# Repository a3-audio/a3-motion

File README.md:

# A³ Motion

The 4-channel motion sampler of [A³ Audio](https://github.com/a3-audio/a3-system).
It records movements on a touchscreen sphere and plays them back in time with
the beat, steering each channel's position on A³ Core over OSC.

This repository holds the panel firmware (`firmware/`, ESP32-S3) and the PCB and
housing designs (`hardware/`; the boards in `pcb/`, one folder per revision: `v1` the first boards (mainboard and button matrix), `v3_1` the current one). The touchscreen app is
[a3-motion-ui](https://github.com/a3-audio/a3-motion-ui), wired in here as the
submodule `a3-motion-ui` (named `ui` until 2026-10-31: every submodule path is
now its repository's name).

**Documentation: https://a3-audio.github.io/a3-doc/**

- [A³ Motion user guide](https://a3-audio.github.io/a3-doc/user/a3motion.html)
- [Configuration](https://a3-audio.github.io/a3-doc/configuration/moc.html),
  [Assembly](https://a3-audio.github.io/a3-doc/assembly/moc.html) and
  [Development](https://a3-audio.github.io/a3-doc/development/moc.html)

## Firmware

A PlatformIO project for the `esp32-s3-devkitc-1-n16r8`. Run from `firmware/`:

```bash
pio run                    # build
pio run -t upload          # flash
pio device monitor         # serial monitor, 115200 baud
pio test -e native         # host-side unit tests
python3 -m unittest test_host
```

Upload and monitor need no port. They find the panel by its USB ID, the CH343
bridge `1A86:55D3` (`build.hwids` in `boards/esp32-s3-devkitc-1-n16r8.json`).

`host.py` polls the firmware over serial and prints the decoded buttons,
encoders and pots (`python3 host.py`; needs `pyserial`). Its docstring lists
the options and describes the binary poll-frame protocol. Use it to tell a
firmware fault from a fault in the UI.

## The UI computer

Motion UI runs on any Linux machine with a touchscreen, and the panel connects
to it over USB. It is tested on a NUC (on the rig, the Core machine) and was
first planned for a Raspberry Pi 5; see
[Hardware](https://a3-audio.github.io/a3-doc/configuration/moc.html#moc-hardware)
in the docs. The i3 config, the X rules and the user service are in the UI
repository, under
[`platform_config/`](https://github.com/a3-audio/a3-motion-ui/tree/main/platform_config).

## License

REUSE-compliant: the licenses are in `LICENSES/`, which file has which is in
`.reuse/dep5`.

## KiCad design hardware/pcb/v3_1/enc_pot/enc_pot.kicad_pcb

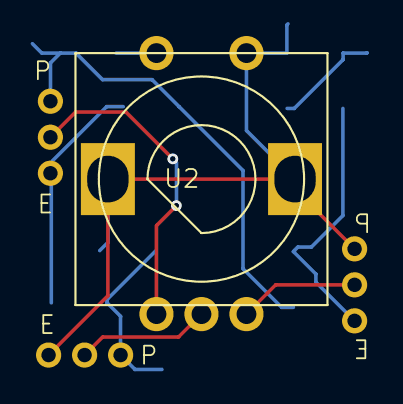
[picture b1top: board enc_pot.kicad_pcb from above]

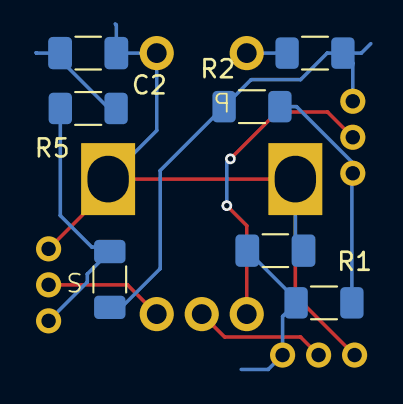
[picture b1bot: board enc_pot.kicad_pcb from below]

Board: 2 copper layers, 11 parts (10 on the bottom side), 10 nets.

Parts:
C1, C2: 100nF; C_1206_3216Metric_Pad1.33x1.80mm_HandSolder
R1, R5: 1k; R_1206_3216Metric_Pad1.30x1.75mm_HandSolder
R2, R4: 10K; R_1206_3216Metric_Pad1.30x1.75mm_HandSolder
R3: 10k; R_1206_3216Metric_Pad1.30x1.75mm_HandSolder
U1, U3, U4: a3_jumper_fix
U2: A3_ENC_POT_mix

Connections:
+3V3: R2.1, R3.2, R4.1, U1.S2
/EB/-: C2.1, R5.1
/ESW: R3.1, U2.S2
GND: C1.2, C2.2, U2.S1, U2.SH1 (shield), U2.SH2 (shield), U3.S2, U4.S1
unnamed: R1.2, R2.2, U1.S1
unnamed: R4.2, R5.2, U4.S2
unnamed: U1.S, U2.A (E1/PA)
unnamed: U2.B (E2/PB), U4.S
unnamed: U2.C (EGND/PW), U3.S
POT_H: C1.1, R1.1, U3.S1

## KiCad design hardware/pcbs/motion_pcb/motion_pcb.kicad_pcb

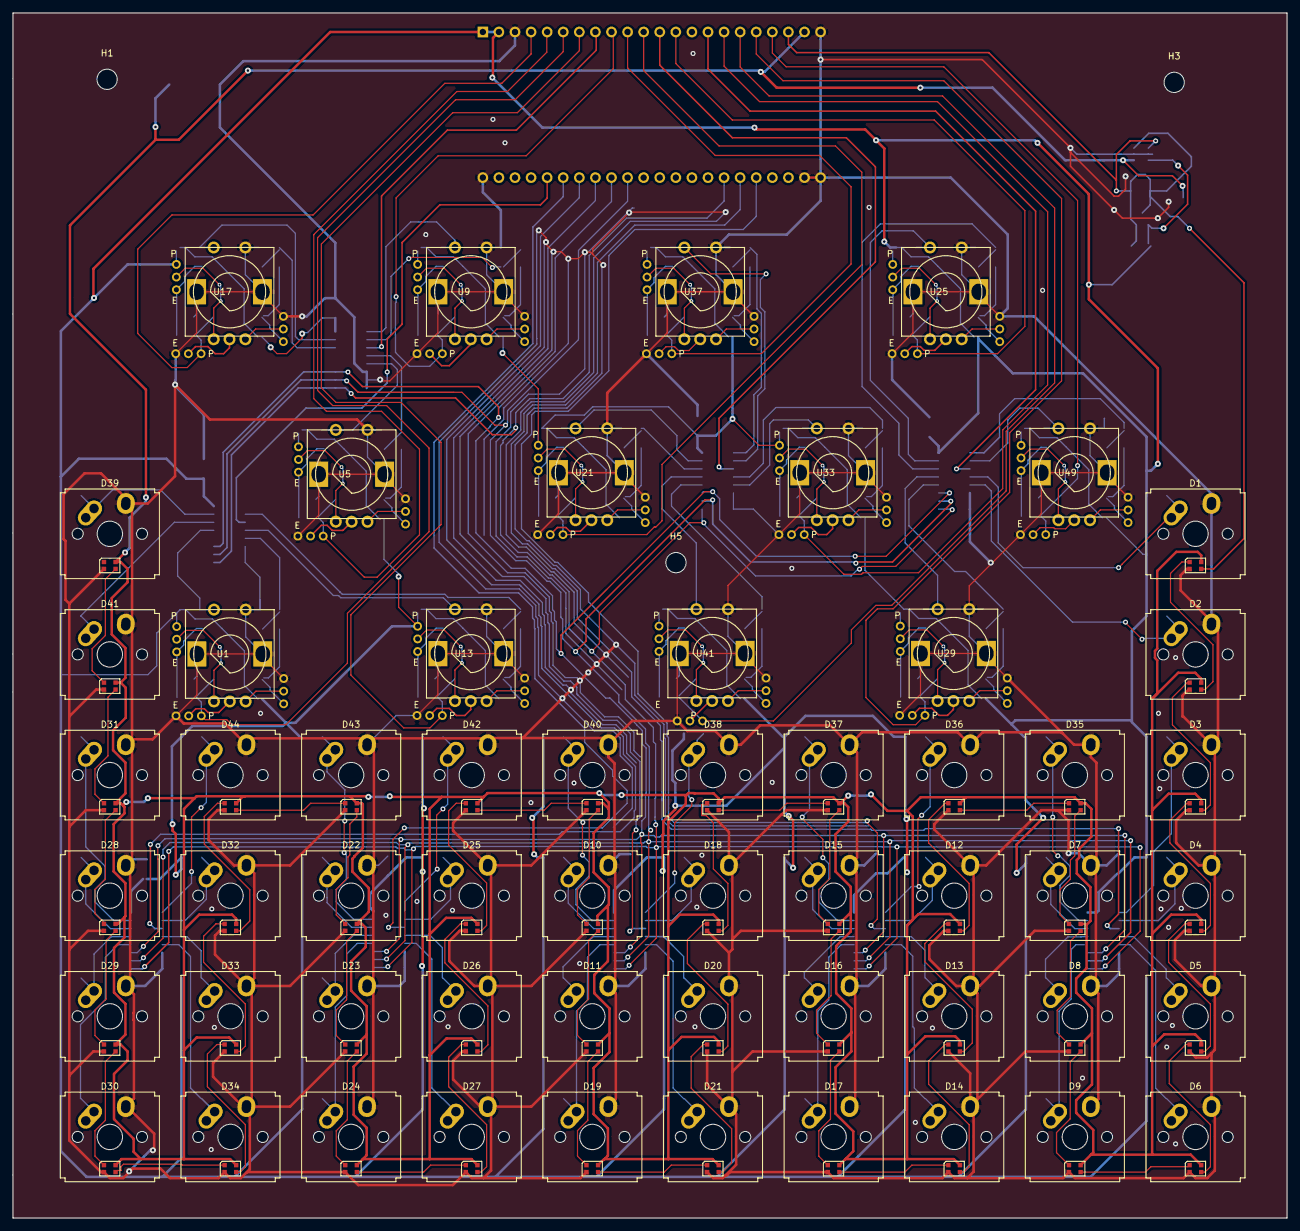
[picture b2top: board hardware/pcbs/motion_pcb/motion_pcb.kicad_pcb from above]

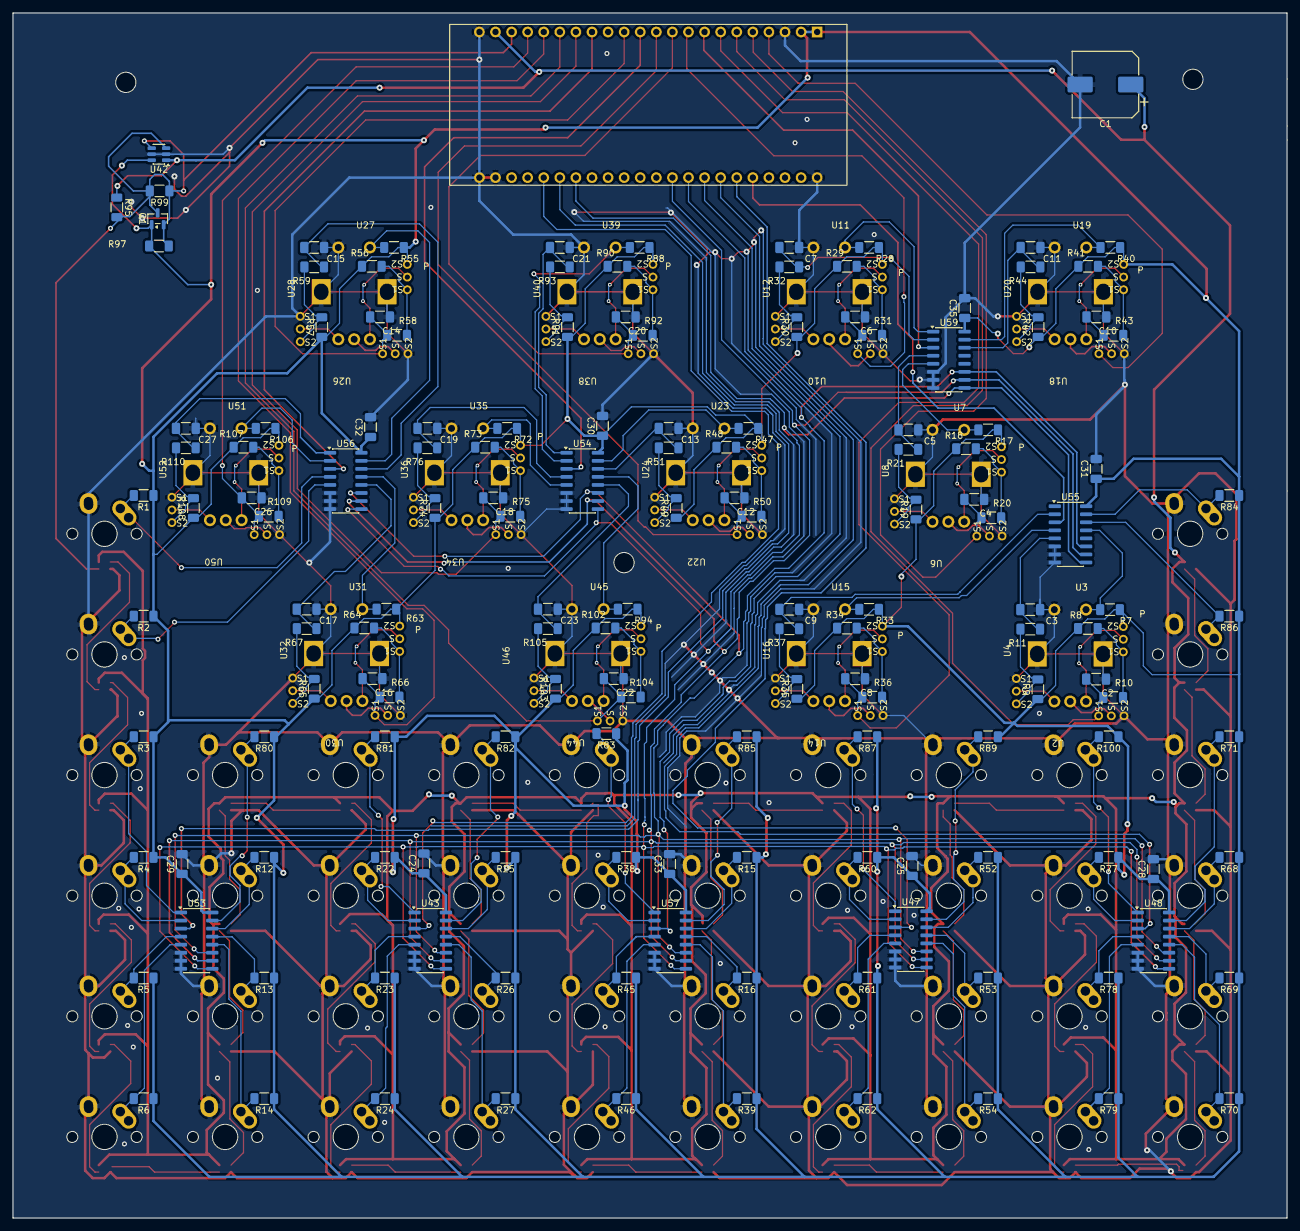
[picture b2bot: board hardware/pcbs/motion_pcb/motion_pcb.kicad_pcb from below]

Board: 2 copper layers, 201.2 x 190.3 mm, 251 parts (189 on the bottom side), 199 nets.

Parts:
C1: 10v/1mF; CP_Elec_10x10
C2, C3, C4, C5, C6, C7, C8, C9, C10, C11, C12, C13, C14, C15, C16, C17, C18, C19, C20, C21, C22, C23, C24, C25, C26, C27, C28, C29, C30, C31, C32, C33, C35: 100nF; C_1206_3216Metric_Pad1.33x1.80mm_HandSolder
D1, D2, D3, D4, D5, D6, D7, D8, D9, D10, D11, D12, D13, D14, D15, D16, D17, D18, D19, D20, D21, D22, D23, D24, D25, D26, D27, D28, D29, D30, D31, D32, D33, D34, D35, D36, D37, D38, D39, D40, D41, D42, D43, D44: WS2812B-2020; A3_CherryMxHybrid_WS2812Led2020
H1, H2, H3, H4, H5, H6: MountingHole; MountingHole_3.2mm_M3
IC1: ESP32-S3-DevKitC-1
Q1: BSS138; SOT-23
R1, R2, R3, R4, R5, R6, R7, R12, R13, R14, R15, R16, R17, R22, R23, R24, R25, R26, R27, R28, R33, R38, R39, R40, R45, R46, R47, R52, R53, R54, R55, R60, R61, R62, R63, R68, R69, R70, R71, R72, R77, R78, R79, R80, R81, R82, R83, R84, R85, R86, R87, R88, R89, R94, R97, R100, R106: 10k; R_1206_3216Metric_Pad1.30x1.75mm_HandSolder
R8, R9, R18, R19, R29, R30, R34, R35, R41, R42, R48, R49, R56, R57, R64, R65, R73, R74, R90, R91, R102, R103, R107, R108: 10K; R_1206_3216Metric_Pad1.30x1.75mm_HandSolder
R10, R11, R20, R21, R31, R32, R36, R37, R43, R44, R50, R51, R58, R59, R66, R67, R75, R76, R92, R93, R95, R104, R105, R109, R110: 1k; R_1206_3216Metric_Pad1.30x1.75mm_HandSolder
R99: 0; R_1206_3216Metric_Pad1.30x1.75mm_HandSolder
U1, U5, U9, U13, U17, U21, U25, U29, U33, U37, U41, U49: A3_ENC_POT_mix
U2, U3, U4, U6, U7, U8, U10, U11, U12, U14, U15, U16, U18, U19, U20, U22, U23, U24, U26, U27, U28, U30, U31, U32, U34, U35, U36, U38, U39, U40, U44, U45, U46, U50, U51, U52: a3_jumper_fix
U42: SN74LVC1T45DBV; SOT-23-6
U43, U47, U48, U53, U54, U55, U56, U57, U59: 74HC4051; SOIC-16_3.9x9.9mm_P1.27mm

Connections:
+3V3: C24.1, C25.1, C28.1, C29.1, C30.1, C31.1, C32.1, C33.1, C35.1, IC1.1 (3v3), IC1.2 (3v3), Q1.1 (G), R1.1, R2.1, R3.1, R4.1, R5.1, R6.1, R7.2, R8.1, R9.1, R12.1, R13.1, R14.1, R15.1, R16.1, R17.2, R18.1, R19.1, R22.1, R23.1, R24.1, R25.1, R26.1, R27.1, R28.2, R29.1, R30.1, R33.2, R34.1, R35.1, R38.1, R39.1, R40.2, R41.1, R42.1, R45.1, R46.1, R47.2, R48.1, R49.1, R52.1, R53.1, R54.1, R55.2, R56.1, R57.1, R60.1, R61.1, R62.1, R63.2, R64.1, R65.1, R68.1, R69.1, R70.1, R71.1, R72.2, R73.1, R74.1, R77.1, R78.1, R79.1, R80.1, R81.1, R82.1, R83.1, R84.1, R85.1, R86.1, R87.1, R88.2, R89.1, R90.1, R91.1, R94.2, R97.1, R100.1, R102.1, R103.1, R106.2, R107.1, R108.1, U2.S2, U6.S2, U10.S2, U14.S2, U18.S2, U22.S2, U26.S2, U30.S2, U34.S2, U38.S2, U42.6 (VCCB), U43.16 (VCC), U44.S2, U47.16 (VCC), U48.16 (VCC), U50.S2, U53.16 (VCC), U54.16 (VCC), U55.16 (VCC), U56.16 (VCC), U57.16 (VCC), U59.16 (VCC)
+5V: C1.1, D1.4 (VCC), D2.4 (VCC), D3.4 (VCC), D4.4 (VCC), D5.4 (VCC), D6.4 (VCC), D7.4 (VCC), D8.4 (VCC), D9.4 (VCC), D10.4 (VCC), D11.4 (VCC), D12.4 (VCC), D13.4 (VCC), D14.4 (VCC), D15.4 (VCC), D16.4 (VCC), D17.4 (VCC), D18.4 (VCC), D19.4 (VCC), D20.4 (VCC), D21.4 (VCC), D22.4 (VCC), D23.4 (VCC), D24.4 (VCC), D25.4 (VCC), D26.4 (VCC), D27.4 (VCC), D28.4 (VCC), D29.4 (VCC), D30.4 (VCC), D31.4 (VCC), D32.4 (VCC), D33.4 (VCC), D34.4 (VCC), D35.4 (VCC), D36.4 (VCC), D37.4 (VCC), D38.4 (VCC), D39.4 (VCC), D40.4 (VCC), D41.4 (VCC), D42.4 (VCC), D43.4 (VCC), D44.4 (VCC), IC1.21 (5V), R95.1, U42.1 (VCCA)
/LED/LedBut1/LED_OUT: D1.1 (DOUT), D2.3 (DIN)
/LED/LedBut2/LED_OUT: D2.1 (DOUT), D3.3 (DIN)
/LED/LedBut3/LED_OUT: D3.1 (DOUT), D4.3 (DIN)
/LED/LedBut4/LED_OUT: D4.1 (DOUT), D5.3 (DIN)
/LED/LedBut5/LED_OUT: D5.1 (DOUT), D6.3 (DIN)
/LED/LedBut8/LED_IN: D7.3 (DIN), D8.1 (DOUT)
/LED/LedBut10/LED_IN: D6.1 (DOUT), D9.3 (DIN)
/LED/LedBut10/LED_OUT: D8.3 (DIN), D9.1 (DOUT)
/LED/LedBut13/LED_IN: D12.3 (DIN), D36.1 (DOUT)
/LED/LedBut13/LED_OUT: D12.1 (DOUT), D13.3 (DIN)
/LED/LedBut14/LED_OUT: D13.1 (DOUT), D14.3 (DIN)
/LED/LedBut15/LED_OUT: D14.1 (DOUT), D17.3 (DIN)
/LED/LedBut16/LED_IN: D15.3 (DIN), D16.1 (DOUT)
/LED/LedBut16/LED_OUT: D15.1 (DOUT), D37.3 (DIN)
/LED/LedBut17/LED_IN: D16.3 (DIN), D17.1 (DOUT)
/LED/LedBut21/LED_IN: D18.3 (DIN), D38.1 (DOUT)
/LED/LedBut21/LED_OUT: D18.1 (DOUT), D20.3 (DIN)
/LED/LedBut22/LED_IN: D10.3 (DIN), D11.1 (DOUT)
/LED/LedBut22/LED_OUT: D10.1 (DOUT), D40.3 (DIN)
/LED/LedBut23/LED_OUT: D20.1 (DOUT), D21.3 (DIN)
/LED/LedBut24/LED_OUT: D19.3 (DIN), D21.1 (DOUT)
/LED/LedBut25/LED_IN: D11.3 (DIN), D19.1 (DOUT)
/LED/LedBut28/LED_IN: D22.3 (DIN), D23.1 (DOUT)
/LED/LedBut28/LED_OUT: D22.1 (DOUT), D43.3 (DIN)
/LED/LedBut30/LED_IN: D25.3 (DIN), D42.1 (DOUT)
/LED/LedBut30/LED_OUT: D25.1 (DOUT), D26.3 (DIN)
/LED/LedBut31/LED_OUT: D26.1 (DOUT), D27.3 (DIN)
/LED/LedBut32/LED_OUT: D24.3 (DIN), D27.1 (DOUT)
/LED/LedBut33/LED_IN: D23.3 (DIN), D24.1 (DOUT)
/LED/LedBut36/LED_IN: D28.3 (DIN), D29.1 (DOUT)
/LED/LedBut36/LED_OUT: D28.1 (DOUT), D31.3 (DIN)
/LED/LedBut37/LED_IN: D29.3 (DIN), D30.1 (DOUT)
/LED/LedBut39/LED_IN: D32.3 (DIN), D44.1 (DOUT)
/LED/LedBut39/LED_OUT: D32.1 (DOUT), D33.3 (DIN)
/LED/LedBut40/LED_OUT: D33.1 (DOUT), D34.3 (DIN)
/LED/LedBut41/LED_OUT: D30.3 (DIN), D34.1 (DOUT)
/LED/LedBut45/LED_OUT: D31.1 (DOUT), D41.3 (DIN)
/LED/LedBut47/LED_IN: D39.3 (DIN), D41.1 (DOUT)
/LED/LedBut55/LED_IN: D7.1 (DOUT), D35.3 (DIN)
/LED/LedBut55/LED_OUT: D35.1 (DOUT), D36.3 (DIN)
/LED/LedBut57/LED_OUT: D37.1 (DOUT), D38.3 (DIN)
/LED/LedBut59/LED_OUT: D40.1 (DOUT), D42.3 (DIN)
/LED/LedBut61/LED_OUT: D43.1 (DOUT), D44.3 (DIN)
/LED/SW00: D39.5 (sw1), R84.2, U55.15 (A2)
/LED/SW09: D1.5 (sw1), R1.2, U56.4 (A7)
/LED/SW10: D41.5 (sw1), R86.2, U55.14 (A1)
/LED/SW19: D2.5 (sw1), R2.2, U56.5 (A5)
/LED/SW20: D31.5 (sw1), R71.2, U48.15 (A2)
/LED/SW21: D44.5 (sw1), R100.2, U48.1 (A4)
/LED/SW22: D43.5 (sw1), R89.2, U47.15 (A2)
/LED/SW23: D42.5 (sw1), R87.2, U47.1 (A4)
/LED/SW24: D40.5 (sw1), R85.2, U57.15 (A2)
/LED/SW25: D38.5 (sw1), R83.2, U57.1 (A4)
/LED/SW26: D37.5 (sw1), R82.2, U43.15 (A2)
/LED/SW27: D36.5 (sw1), R81.2, U43.1 (A4)
/LED/SW28: D35.5 (sw1), R80.2, U53.15 (A2)
/LED/SW29: D3.5 (sw1), R3.2, U53.1 (A4)
/LED/SW30: D28.5 (sw1), R68.2, U48.14 (A1)
/LED/SW31: D32.5 (sw1), R77.2, U48.2 (A6)
/LED/SW32: D22.5 (sw1), R52.2, U47.14 (A1)
/LED/SW33: D25.5 (sw1), R60.2, U47.2 (A6)
/LED/SW34: D10.5 (sw1), R15.2, U57.14 (A1)
/LED/SW35: D18.5 (sw1), R38.2, U57.2 (A6)
/LED/SW36: D15.5 (sw1), R25.2, U43.14 (A1)
/LED/SW37: D12.5 (sw1), R22.2, U43.2 (A6)
/LED/SW38: D7.5 (sw1), R12.2, U53.14 (A1)
/LED/SW39: D4.5 (sw1), R4.2, U53.2 (A6)
/LED/SW40: D29.5 (sw1), R69.2, U48.13 (A0)
/LED/SW41: D33.5 (sw1), R78.2, U48.4 (A7)
/LED/SW42: D23.5 (sw1), R53.2, U47.13 (A0)
/LED/SW43: D26.5 (sw1), R61.2, U47.4 (A7)
/LED/SW44: D11.5 (sw1), R16.2, U57.13 (A0)
/LED/SW45: D20.5 (sw1), R45.2, U57.4 (A7)
/LED/SW46: D16.5 (sw1), R26.2, U43.13 (A0)
/LED/SW47: D13.5 (sw1), R23.2, U43.4 (A7)
/LED/SW48: D8.5 (sw1), R13.2, U53.13 (A0)
/LED/SW49: D5.5 (sw1), R5.2, U53.4 (A7)
/LED/SW50: D30.5 (sw1), R70.2, U48.12 (A3)
/LED/SW51: D34.5 (sw1), R79.2, U48.5 (A5)
/LED/SW52: D24.5 (sw1), R54.2, U47.12 (A3)
/LED/SW53: D27.5 (sw1), R62.2, U47.5 (A5)
/LED/SW54: D19.5 (sw1), R39.2, U57.12 (A3)
/LED/SW55: D21.5 (sw1), R46.2, U57.5 (A5)
/LED/SW56: D17.5 (sw1), R27.2, U43.12 (A3)
/LED/SW57: D14.5 (sw1), R24.2, U43.5 (A5)
/LED/SW58: D9.5 (sw1), R14.2, U53.12 (A3)
/LED/SW59: D6.5 (sw1), R6.2, U53.5 (A5)
/mux/EB01: C11.1, R44.1, U59.14 (A1)
/mux/EB03: C7.1, R32.1, U59.2 (A6)
/mux/EB05: C21.1, R93.1, U54.1 (A4)
/mux/EB07: C15.1, R59.1, U56.14 (A1)
/mux/EB12: C5.1, R21.1, U59.4 (A7)
/mux/EB14: C13.1, R51.1, U54.14 (A1)
/mux/EB16: C19.1, R76.1, U54.4 (A7)
/mux/EB18: C27.1, R110.1, U56.1 (A4)
/mux/EB21: C3.1, R11.1, U55.5 (A5)
/mux/EB23: C9.1, R37.1, U55.2 (A6)
/mux/EB25: C23.1, R105.1, U54.12 (A3)
/mux/EB27: C17.1, R67.1, U56.12 (A3)
/mux/ES01: R40.1, U17.S2, U59.15 (A2)
/mux/ES03: R28.1, U9.S2, U59.1 (A4)
/mux/ES05: R88.1, U37.S2, U54.2 (A6)
/mux/ES07: R55.1, U25.S2, U56.15 (A2)
/mux/ES12: R17.1, U5.S2, U59.5 (A5)
/mux/ES14: R47.1, U21.S2, U54.15 (A2)
/mux/ES16: R72.1, U33.S2, U54.5 (A5)
/mux/ES18: R106.1, U49.S2, U56.2 (A6)
/mux/ES21: R7.1, U1.S2, U55.13 (A0)
/mux/ES23: R33.1, U13.S2, U55.4 (A7)
/mux/ES25: R94.1, U41.S2, U54.13 (A0)
/mux/ES27: R63.1, U29.S2, U56.13 (A0)
GND: C1.2, C2.2, C3.2, C4.2, C5.2, C6.2, C7.2, C8.2, C9.2, C10.2, C11.2, C12.2, C13.2, C14.2, C15.2, C16.2, C17.2, C18.2, C19.2, C20.2, C21.2, C22.2, C23.2, C24.2, C25.2, C26.2, C27.2, C28.2, C29.2, C30.2, C31.2, C32.2, C33.2, C35.2, D1.2 (GND), D1.6 (sw2), D2.2 (GND), D2.6 (sw2), D3.2 (GND), D3.6 (sw2), D4.2 (GND), D4.6 (sw2), D5.2 (GND), D5.6 (sw2), D6.2 (GND), D6.6 (sw2), D7.2 (GND), D7.6 (sw2), D8.2 (GND), D8.6 (sw2), D9.2 (GND), D9.6 (sw2), D10.2 (GND), D10.6 (sw2), D11.2 (GND), D11.6 (sw2), D12.2 (GND), D12.6 (sw2), D13.2 (GND), D13.6 (sw2), D14.2 (GND), D14.6 (sw2), D15.2 (GND), D15.6 (sw2), D16.2 (GND), D16.6 (sw2), D17.2 (GND), D17.6 (sw2), D18.2 (GND), D18.6 (sw2), D19.2 (GND), D19.6 (sw2), D20.2 (GND), D20.6 (sw2), D21.2 (GND), D21.6 (sw2), D22.2 (GND), D22.6 (sw2), D23.2 (GND), D23.6 (sw2), D24.2 (GND), D24.6 (sw2), D25.2 (GND), D25.6 (sw2), D26.2 (GND), D26.6 (sw2), D27.2 (GND), D27.6 (sw2), D28.2 (GND), D28.6 (sw2), D29.2 (GND), D29.6 (sw2), D30.2 (GND), D30.6 (sw2), D31.2 (GND), D31.6 (sw2), D32.2 (GND), D32.6 (sw2), D33.2 (GND), D33.6 (sw2), D34.2 (GND), D34.6 (sw2), D35.2 (GND), D35.6 (sw2), D36.2 (GND), D36.6 (sw2), D37.2 (GND), D37.6 (sw2), D38.2 (GND), D38.6 (sw2), D39.2 (GND), D39.6 (sw2), D40.2 (GND), D40.6 (sw2), D41.2 (GND), D41.6 (sw2), D42.2 (GND), D42.6 (sw2), D43.2 (GND), D43.6 (sw2), D44.2 (GND), D44.6 (sw2), IC1.3 (RST), IC1.22 (GND), IC1.23 (GND), IC1.24 (GND), IC1.44 (GND), U1.S1, U1.SH1 (shield), U1.SH2 (shield), U3.S1, U4.S2, U5.S1, U5.SH1 (shield), U5.SH2 (shield), U7.S1, U8.S2, U9.S1, U9.SH1 (shield), U9.SH2 (shield), U11.S1, U12.S2, U13.S1, U13.SH1 (shield), U13.SH2 (shield), U15.S1, U16.S2, U17.S1, U17.SH1 (shield), U17.SH2 (shield), U19.S1, U20.S2, U21.S1, U21.SH1 (shield), U21.SH2 (shield), U23.S1, U24.S2, U25.S1, U25.SH1 (shield), U25.SH2 (shield), U27.S1, U28.S2, U29.S1, U29.SH1 (shield), U29.SH2 (shield), U31.S1, U32.S2, U33.S1, U33.SH1 (shield), U33.SH2 (shield), U35.S1, U36.S2, U37.S1, U37.SH1 (shield), U37.SH2 (shield), U39.S1, U40.S2, U41.S1, U41.SH1 (shield), U41.SH2 (shield), U42.2 (GND), U42.5 (DIR), U43.6 (~E), U43.7 (VEE), U43.8 (GND), U45.S1, U46.S2, U47.6 (~E), U47.7 (VEE), U47.8 (GND), U48.6 (~E), U48.7 (VEE), U48.8 (GND), U49.S1, U49.SH1 (shield), U49.SH2 (shield), U51.S1, U52.S2, U53.6 (~E), U53.7 (VEE), U53.8 (GND), U54.6 (~E), U54.7 (VEE), U54.8 (GND), U55.6 (~E), U55.7 (VEE), U55.8 (GND), U56.6 (~E), U56.7 (VEE), U56.8 (GND), U57.6 (~E), U57.7 (VEE), U57.8 (GND), U59.6 (~E), U59.7 (VEE), U59.8 (GND)
MA: IC1.40 (IO2/AD1_1), U55.3 (A)
MAA01: IC1.38 (IO41), U48.3 (A)
MAA23: IC1.39 (IO42), U47.3 (A)
MAA45: IC1.37 (IO40), U57.3 (A)
MAA67: IC1.27 (IO21), U43.3 (A)
MAA89: IC1.28 (IO47), U53.3 (A)
MB: IC1.8 (IO15/AD2_4), U59.3 (A)
MC: IC1.12 (IO8/AD1_7), U54.3 (A)
MD: IC1.15 (IO9/AD1_8), U56.3 (A)
MEA01: C10.1, IC1.4 (IO4/AD1_3), R43.1, U20.S1
MEA03: C6.1, IC1.9 (IO16/AD2_5), R31.1, U12.S1
MEA05: C20.1, IC1.10 (IO17/AD2_6), R92.1, U40.S1
MEA07: C14.1, IC1.13 (IO3/AD1_2), R58.1, U28.S1
MEA12: C4.1, IC1.5 (IO5/AD1_4), R20.1, U8.S1
MEA14: C12.1, IC1.11 (IO18/AD2_7), R50.1, U24.S1
MEA16: C18.1, IC1.16 (IO10/AD1_9), R75.1, U36.S1
MEA18: C26.1, IC1.19 (IO13/AD2_2), R109.1, U52.S1
MEA21: C2.1, IC1.6 (IO6/AD1_5), R10.1, U4.S1
MEA23: C8.1, IC1.7 (IO7/AD1_6), R36.1, U16.S1
MEA25: C22.1, IC1.17 (IO11/AD2_0), R104.1, U46.S1
MEA27: C16.1, IC1.18 (IO12/AD2_1), R66.1, U32.S1
MS0: IC1.36 (IO39), U43.11 (S0), U47.11 (S0), U48.11 (S0), U53.11 (S0), U54.11 (S0), U55.11 (S0), U56.11 (S0), U57.11 (S0), U59.11 (S0)
MS1: IC1.35 (IO38/LED), U43.10 (S1), U47.10 (S1), U48.10 (S1), U53.10 (S1), U54.10 (S1), U55.10 (S1), U56.10 (S1), U57.10 (S1), U59.10 (S1)
MS2: IC1.29 (IO48), U43.9 (S2), U47.9 (S2), U48.9 (S2), U53.9 (S2), U54.9 (S2), U55.9 (S2), U56.9 (S2), U57.9 (S2), U59.9 (S2)
unnamed: R8.2, R10.2, U2.S1
unnamed: R9.2, R11.2, U3.S2
unnamed: R18.2, R20.2, U6.S1
unnamed: R19.2, R21.2, U7.S2
unnamed: R29.2, R31.2, U10.S1
unnamed: R30.2, R32.2, U11.S2
unnamed: R34.2, R36.2, U14.S1
unnamed: R35.2, R37.2, U15.S2
unnamed: R41.2, R43.2, U18.S1
unnamed: R42.2, R44.2, U19.S2
unnamed: R48.2, R50.2, U22.S1
unnamed: R49.2, R51.2, U23.S2
unnamed: R56.2, R58.2, U26.S1
unnamed: R57.2, R59.2, U27.S2
unnamed: R64.2, R66.2, U30.S1
unnamed: R65.2, R67.2, U31.S2
unnamed: R73.2, R75.2, U34.S1
unnamed: R74.2, R76.2, U35.S2
unnamed: R90.2, R92.2, U38.S1
unnamed: R91.2, R93.2, U39.S2
unnamed: R102.2, R104.2, U44.S1
unnamed: R103.2, R105.2, U45.S2
unnamed: R107.2, R109.2, U50.S1
unnamed: R108.2, R110.2, U51.S2
unnamed: U1.A (E1/PA), U2.S
unnamed: U1.B (E2/PB), U3.S
unnamed: U1.C (EGND/PW), U4.S
unnamed: U5.A (E1/PA), U6.S
unnamed: U5.B (E2/PB), U7.S
unnamed: U5.C (EGND/PW), U8.S
unnamed: U9.A (E1/PA), U10.S
unnamed: U9.B (E2/PB), U11.S
unnamed: U9.C (EGND/PW), U12.S
unnamed: U13.A (E1/PA), U14.S
unnamed: U13.B (E2/PB), U15.S
unnamed: U13.C (EGND/PW), U16.S
unnamed: U17.A (E1/PA), U18.S
unnamed: U17.B (E2/PB), U19.S
unnamed: U17.C (EGND/PW), U20.S
unnamed: U21.A (E1/PA), U22.S
unnamed: U21.B (E2/PB), U23.S
unnamed: U21.C (EGND/PW), U24.S
unnamed: U25.A (E1/PA), U26.S
unnamed: U25.B (E2/PB), U27.S
unnamed: U25.C (EGND/PW), U28.S
unnamed: U29.A (E1/PA), U30.S
unnamed: U29.B (E2/PB), U31.S
unnamed: U29.C (EGND/PW), U32.S
unnamed: U33.A (E1/PA), U34.S
unnamed: U33.B (E2/PB), U35.S
unnamed: U33.C (EGND/PW), U36.S
unnamed: U37.A (E1/PA), U38.S
unnamed: U37.B (E2/PB), U39.S
unnamed: U37.C (EGND/PW), U40.S
unnamed: U41.A (E1/PA), U44.S
unnamed: U41.B (E2/PB), U45.S
unnamed: U41.C (EGND/PW), U46.S
unnamed: U49.A (E1/PA), U50.S
unnamed: U49.B (E2/PB), U51.S
unnamed: U49.C (EGND/PW), U52.S
led_dat: D1.3 (DIN), IC1.20 (IO14/AD2_3), Q1.2 (S), Q1.3 (D), R95.2, R97.2, R99.1, R99.2, U42.3 (A), U42.4 (B)

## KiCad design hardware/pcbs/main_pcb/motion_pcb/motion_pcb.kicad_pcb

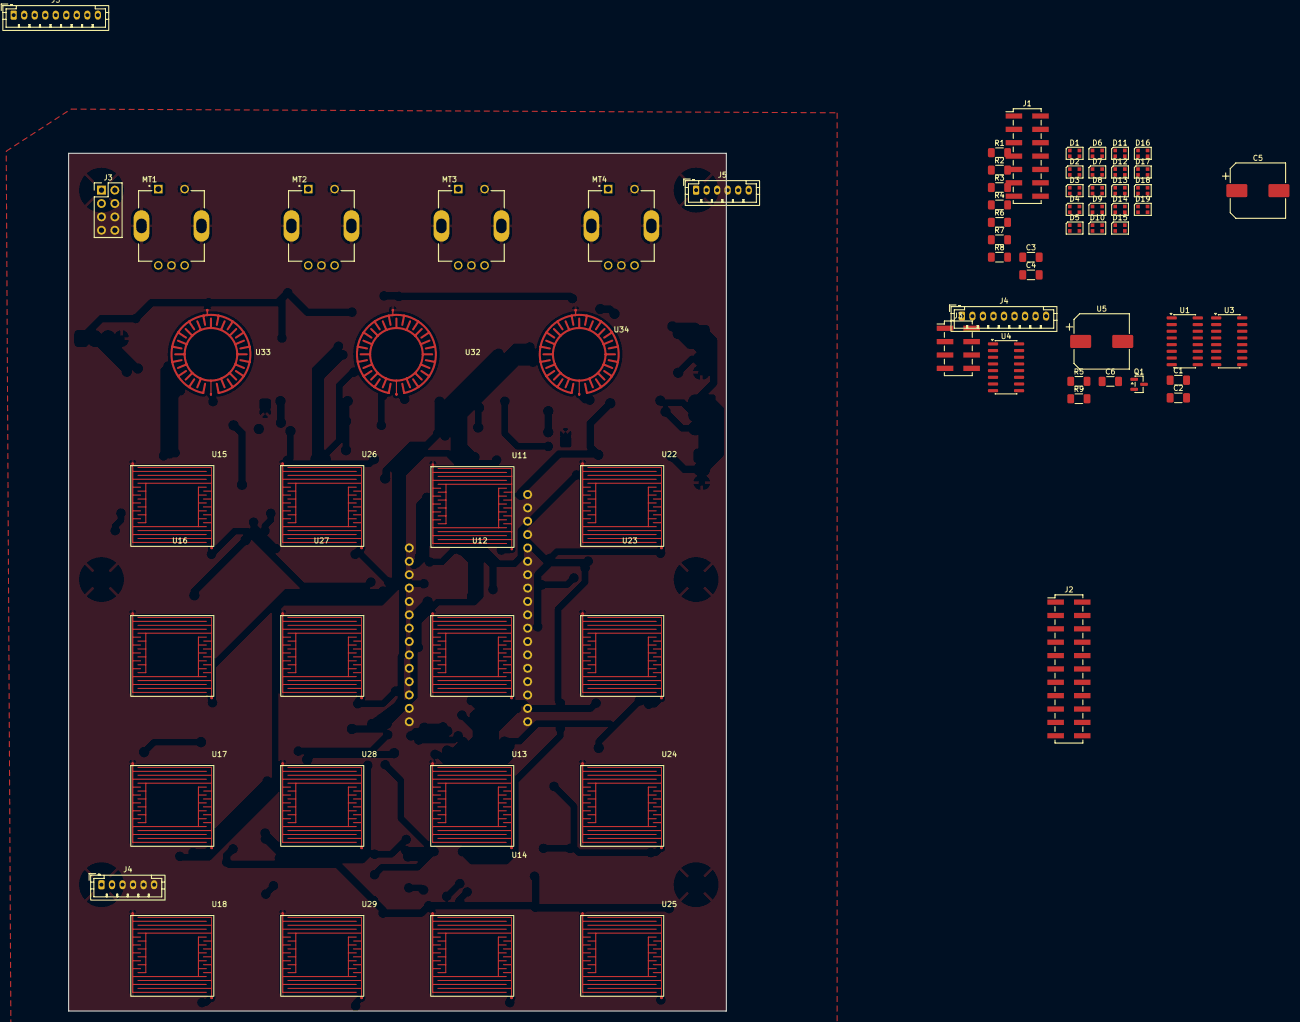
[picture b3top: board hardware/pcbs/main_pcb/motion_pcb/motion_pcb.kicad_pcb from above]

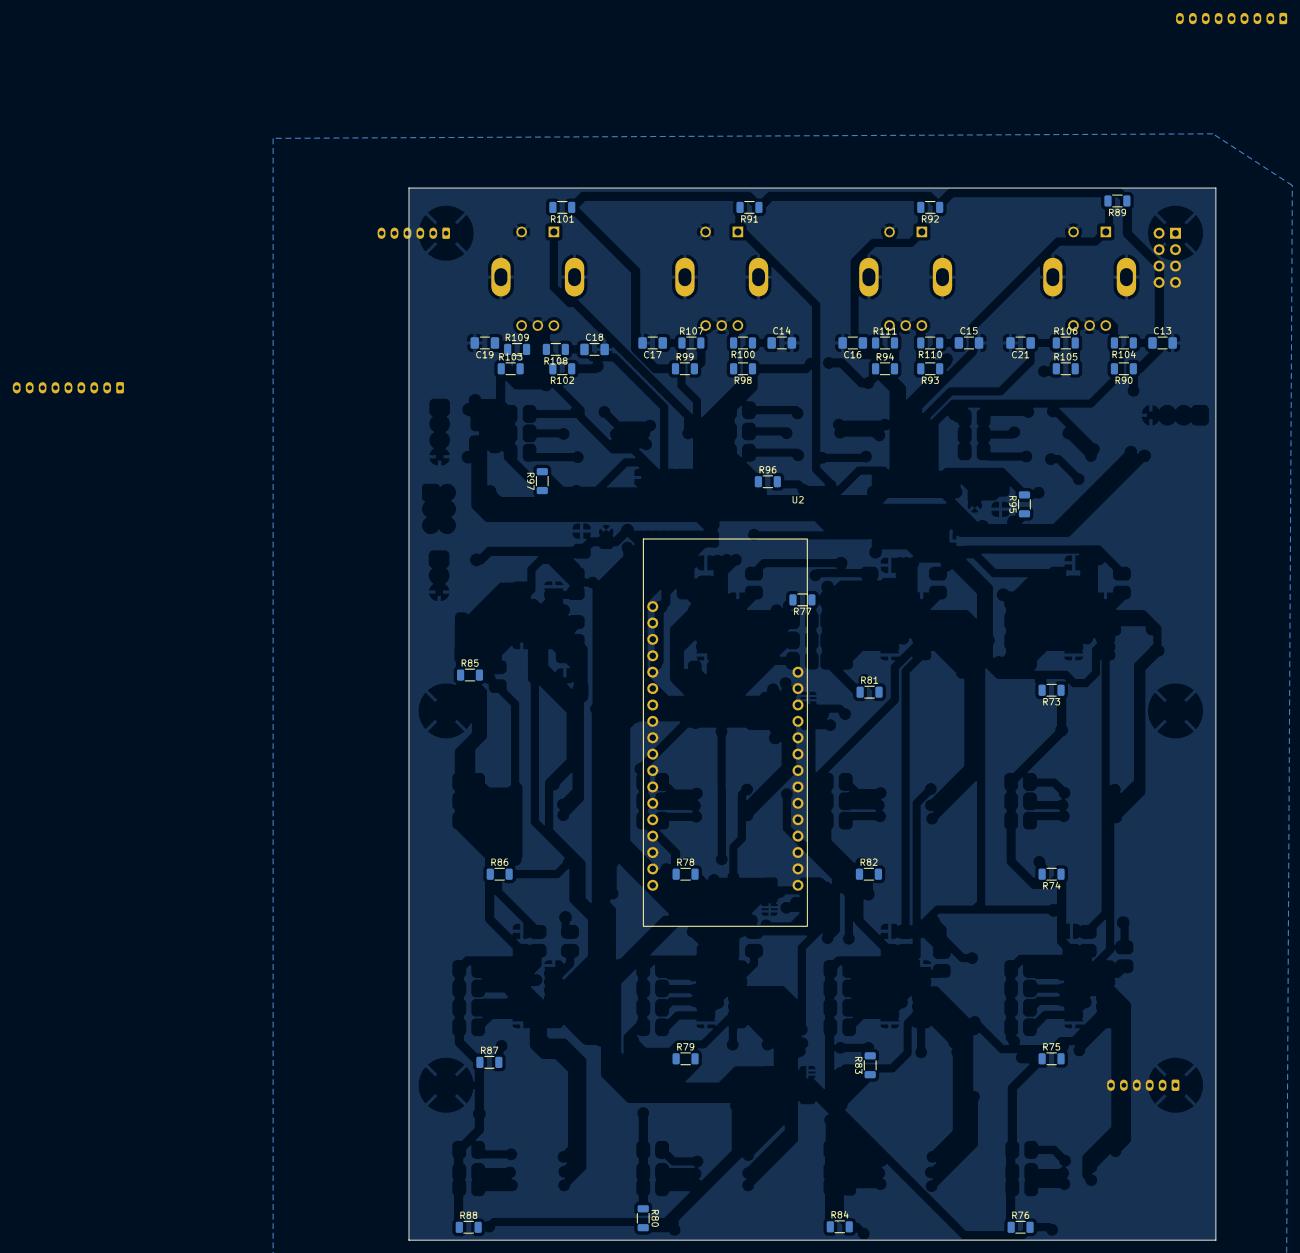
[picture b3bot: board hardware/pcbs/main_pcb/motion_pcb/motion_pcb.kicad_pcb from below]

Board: 2 copper layers, 125.0 x 163.0 mm, 124 parts (48 on the bottom side), 78 nets, no tracks yet.

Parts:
C1, C2, C3, C4, C6, C13, C14, C15, C16, C17, C18, C19, C21: 100nF; C_1206_3216Metric_Pad1.33x1.80mm_HandSolder
C5: 10v/1mF; CP_Elec_10x10
D1, D2, D3, D4, D5, D6, D7, D8, D9, D10, D11, D12, D13, D14, D15, D16, D17, D18, D19: WS2812B-2020; LED_WS2812B-2020_PLCC4_2.0x2.0mm
H1, H2, H3, H4, H5, H6: MountingHole; MountingHole_3.2mm_M3
J1: esp_io_shield1; PinHeader_2x07_P2.54mm_Vertical_SMD
J2: esp_io_shield2; PinHeader_2x11_P2.54mm_Vertical_SMD
J3: esp32_voltage_shield; PinHeader_2x04_P2.54mm_Vertical_SMD
J3#2: esp32_voltage_shield; PinHeader_2x04_P2.54mm_Vertical
J4: Con_top_pcb; JST_PH_B9B-PH-K_1x09_P2.00mm_Vertical
J4#2: Con_top_pcb; JST_PH_B6B-PH-K_1x06_P2.00mm_Vertical
J5: con_rpi; JST_PH_B6B-PH-K_1x06_P2.00mm_Vertical
J5#2: con_rpi; JST_PH_B9B-PH-K_1x09_P2.00mm_Vertical
MT1, MT2, MT3, MT4: PEC11R-4215F-S0024; XDCR_PEC11R-4215F-S0024
Q1: BSS138; SOT-23
R1, R2, R3, R4, R6, R7, R8: 100; R_1206_3216Metric_Pad1.30x1.75mm_HandSolder
R5: 1k; R_1206_3216Metric_Pad1.30x1.75mm_HandSolder
R9: 10k; R_1206_3216Metric_Pad1.30x1.75mm_HandSolder
R73, R74, R75, R76, R77, R78, R79, R80, R81, R82, R83, R84, R85, R86, R87, R88, R89, R90, R91, R92, R93, R94, R95, R96, R97, R98, R99, R101, R102, R103, R105: 10K; R_1206_3216Metric
R100, R104, R106, R107, R108, R109, R110, R111: 1k; R_1206_3216Metric
U1, U3, U4: 74HC4051; SOIC-16_3.9x9.9mm_P1.27mm
U2: DFR0645
U5: 74AHCT125; CP_Elec_10x10
U11, U12, U13, U14, U15, U16, U17, U18, U22, U23, U24, U25, U26, U27, U28, U29: touch_but_square; But_Velo_Rec_1
U32, U33, U34: touch_but_round; But_Velo_Rnd_1

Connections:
+3V3: C1.1, C2.1, C3.1, J3.3, J3.4, J3#2.3, J3#2.4, J4.1, J4#2.1, Q1.1 (G), R9.1, R73.1, R74.1, R75.1, R76.1, R77.1, R78.1, R79.1, R80.1, R81.1, R82.1, R83.1, R84.1, R85.1, R86.1, R87.1, R88.1, R89.1, R90.1, R91.1, R92.1, R93.1, R94.1, R95.1, R96.1, R97.1, R98.1, R99.1, R101.1, R102.1, R103.1, R105.1, U1.16 (VCC), U2.1 (RST), U2.31 (3V3), U3.16 (VCC), U4.16 (VCC)
+5V: C5.1, C6.1, D1.4 (VDD), D2.4 (VDD), D3.4 (VDD), D4.4 (VDD), D5.4 (VDD), D6.4 (VDD), D7.4 (VDD), D8.4 (VDD), D9.4 (VDD), D10.4 (VDD), D11.4 (VDD), D12.4 (VDD), D13.4 (VDD), D14.4 (VDD), D15.4 (VDD), D16.4 (VDD), D17.4 (VDD), D18.4 (VDD), D19.4 (VDD), J3.1, J3.2, J3#2.1, J3#2.2, J5.1, J5#2.1, R5.1, U2.32 (VCC)
BR1: R95.2, U4.15 (A2), U33.1
BR2: R96.2, U4.14 (A1), U32.1
BR3: R97.2, U4.13 (A0), U34.1
BUTA1: R73.2, U1.13 (A0), U15.1
BUTA2: R74.2, U1.14 (A1), U16.1
BUTA3: R75.2, U1.15 (A2), U17.1
BUTA4: R76.2, U1.12 (A3), U18.1
BUTB1: R81.2, U1.1 (A4), U26.1
BUTB2: R82.2, U1.5 (A5), U27.1
BUTB3: R83.2, U1.2 (A6), U28.1
BUTB4: R84.2, U1.4 (A7), U29.1
BUTC1: R77.2, U3.13 (A0), U11.1
BUTC2: R78.2, U3.14 (A1), U12.1
BUTC3: R79.2, U3.15 (A2), U13.1
BUTC4: R80.2, U3.12 (A3), U14.1
BUTD1: R85.2, U3.1 (A4), U22.1
BUTD2: R86.2, U3.5 (A5), U23.1
BUTD3: R87.2, U3.2 (A6), U24.1
BUTD4: R88.2, U3.4 (A7), U25.1
EA1: C13.1, J1.1, J1.2, R104.1, U2.6 (18/SCK)
EA2: C15.1, J1.7, J1.8, R110.1, U2.12 (13/D7)
EA3: C14.1, J1.11, J1.12, R100.1, U2.15 (26/D3)
EA4: C18.1, J2.15, J2.16, R108.1, U2.22 (12/D13)
EB1: C21.1, J1.5, J1.6, R106.1, U2.8 (19/MISO)
EB2: C16.1, J1.9, J1.10, R111.1, U2.13 (14/D6)
EB3: C17.1, J1.13, J1.14, R107.1, U2.16 (25/D2)
EB4: C19.1, J2.13, J2.14, R109.1, U2.23 (36/A0)
ES1: MT1.1, R89.2, U4.12 (A3)
ES2: MT2.1, R92.2, U4.1 (A4)
ES3: MT3.1, R91.2, U4.5 (A5)
ES4: MT4.1, R101.2, U4.2 (A6)
GND: C1.2, C2.2, C3.2, C4.2, C5.2, C6.2, C13.2, C14.2, C15.2, C16.2, C17.2, C18.2, C19.2, C21.2, D1.2 (VSS), D2.2 (VSS), D3.2 (VSS), D4.2 (VSS), D5.2 (VSS), D6.2 (VSS), D7.2 (VSS), D8.2 (VSS), D9.2 (VSS), D10.2 (VSS), D11.2 (VSS), D12.2 (VSS), D13.2 (VSS), D14.2 (VSS), D15.2 (VSS), D16.2 (VSS), D17.2 (VSS), D18.2 (VSS), D19.2 (VSS), J3.7, J3.8, J3#2.7, J3#2.8, J4.6, J4#2.6, J5.3, J5.5, J5#2.3, J5#2.5, MT1.2, MT1.COM, MT1.S1 (SHIELD), MT1.S2 (SHIELD), MT2.2, MT2.COM, MT2.S1 (SHIELD), MT2.S2 (SHIELD), MT3.2, MT3.COM, MT3.S1 (SHIELD), MT3.S2 (SHIELD), MT4.2, MT4.COM, MT4.S1 (SHIELD), MT4.S2 (SHIELD), U1.6 (~E), U1.7 (VEE), U1.8 (GND), U2.4 (GND), U2.30 (GND), U3.6 (~E), U3.7 (VEE), U3.8 (GND), U4.6 (~E), U4.7 (VEE), U4.8 (GND), U5.1, U11.2, U12.2, U13.2, U14.2, U15.2, U16.2, U17.2, U18.2, U22.2, U23.2, U24.2, U25.2, U26.2, U27.2, U28.2, U29.2, U32.2, U33.2, U34.2
MUX_A: R1.1, U1.3 (A)
MUX_B: R2.1, U3.3 (A)
MUX_C: R3.1, U4.3 (A)
MUX_D: C4.1, J4.2, J4#2.2, R4.1
MUX_S0: J2.17, J2.18, R6.2, U1.11 (S0), U2.21 (4/D12), U3.11 (S0), U4.9 (S2)
MUX_S1: J2.19, J2.20, R7.2, U1.10 (S1), U2.20 (16/D11), U3.10 (S1), U4.10 (S1)
MUX_S2: J2.21, J2.22, R8.2, U1.9 (S2), U2.19 (17/D10), U3.9 (S2), U4.11 (S0)
unnamed: D1.1 (DOUT), D2.3 (DIN)
unnamed: D2.1 (DOUT), D3.3 (DIN)
unnamed: D3.1 (DOUT), D4.3 (DIN)
unnamed: D4.1 (DOUT), D5.3 (DIN)
unnamed: D5.1 (DOUT), D6.3 (DIN)
unnamed: D6.1 (DOUT), D7.3 (DIN)
unnamed: D7.1 (DOUT), D8.3 (DIN)
unnamed: D9.1 (DOUT), D10.3 (DIN)
unnamed: D10.1 (DOUT), D11.3 (DIN)
unnamed: D11.1 (DOUT), D12.3 (DIN)
unnamed: D12.1 (DOUT), D13.3 (DIN)
unnamed: D13.1 (DOUT), D14.3 (DIN)
unnamed: D14.1 (DOUT), D15.3 (DIN)
unnamed: D15.1 (DOUT), D16.3 (DIN)
unnamed: D17.1 (DOUT), D18.3 (DIN)
unnamed: D18.1 (DOUT), D19.3 (DIN)
unnamed: J2.5, J2.6, R1.2, U2.27 (15/A4)
unnamed: J2.7, J2.8, R2.2, U2.26 (35/A3)
unnamed: J2.9, J2.10, R3.2, U2.25 (34/A2)
unnamed: J2.11, J2.12, R4.2, U2.24 (39/A1)
unnamed: J3.5, J3.6, J3#2.5, J3#2.6, U2.2 (3v3)
unnamed: J4.3, J4#2.3, R6.1
unnamed: J4.4, J4#2.4, R7.1
unnamed: J4.5, J4#2.5, R8.1
unnamed: MT1.A, R90.2, R104.2
unnamed: MT1.B, R105.2, R106.2
unnamed: MT2.A, R93.2, R110.2
unnamed: MT2.B, R94.2, R111.2
unnamed: MT3.A, R98.2, R100.2
unnamed: MT3.B, R99.2, R107.2
unnamed: MT4.A, R102.2, R108.2
unnamed: MT4.B, R103.2, R109.2
SCL: J2.1, J2.2, J5.4, J5#2.4, U2.29 (22/SCL)
SDA: J2.3, J2.4, J5.2, J5#2.2, U2.28 (21/SDA)
dat1: D8.1 (DOUT), D9.3 (DIN)
dat2: D16.1 (DOUT), D17.3 (DIN)
led_dat: D1.3 (DIN), J1.3, J1.4, Q1.2 (S), Q1.3 (D), R5.2, R9.2, U2.7 (23/MOSI), U5.2

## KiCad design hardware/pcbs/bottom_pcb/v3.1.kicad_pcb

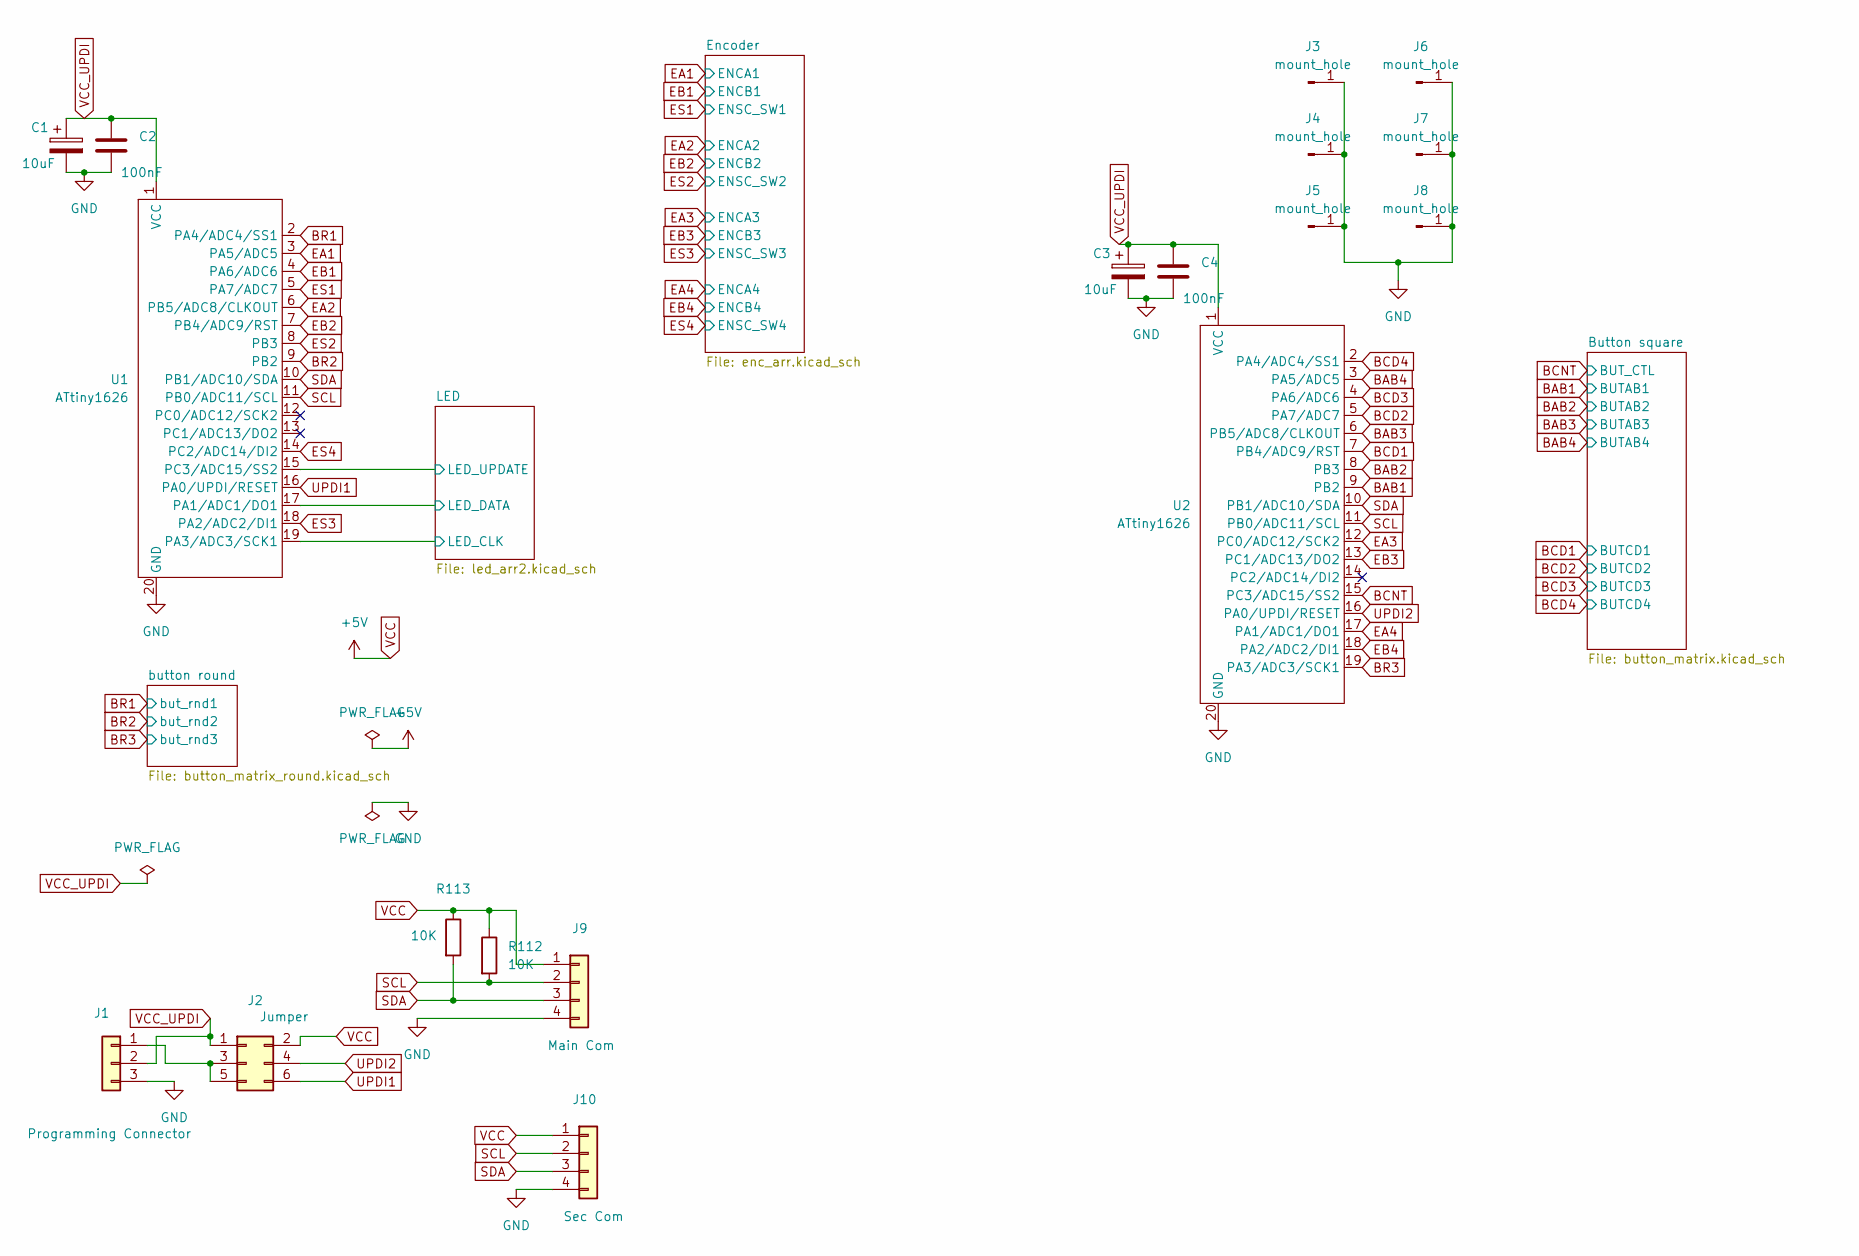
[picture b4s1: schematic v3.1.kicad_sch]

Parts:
C1, C3: 10uF; CP_Radial_D4.0mm_P1.50mm
C2, C4: 100nF; C_1206_3216Metric_Pad1.33x1.80mm_HandSolder
J1: Programming Connector; Molex_KK-254_AE-6410-03A_1x03_P2.54mm_Vertical
J2: Jumper; PinHeader_2x03_P2.54mm_Vertical
J3, J4, J5, J6, J7, J8: mount_hole; MountingHole_4.3mm_M4_DIN965_Pad
J9: Main Com; Molex_KK-254_AE-6410-04A_1x04_P2.54mm_Vertical
J10: Sec Com; Molex_KK-254_AE-6410-04A_1x04_P2.54mm_Vertical
R112, R113: 10K; R_1206_3216Metric
U1, U2: ATtiny1626; attiny1626

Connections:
/LED/LED_CLK: U1.19 (PA3/ADC3/SCK1); also elsewhere on the board
/LED/LED_DATA: U1.17 (PA1/ADC1/DO1); also elsewhere on the board
/LED/LED_UPDATE: U1.15 (PC3/ADC15/SS2); also elsewhere on the board
BAB1: U2.9 (PB2); also elsewhere on the board
BAB2: U2.8 (PB3); also elsewhere on the board
BAB3: U2.6 (PB5/ADC8/CLKOUT); also elsewhere on the board
BAB4: U2.3 (PA5/ADC5); also elsewhere on the board
BCD1: U2.7 (PB4/ADC9/RST); also elsewhere on the board
BCD2: U2.5 (PA7/ADC7); also elsewhere on the board
BCD3: U2.4 (PA6/ADC6); also elsewhere on the board
BCD4: U2.2 (PA4/ADC4/SS1); also elsewhere on the board
BCNT: U2.15 (PC3/ADC15/SS2); also elsewhere on the board
BR1: U1.2 (PA4/ADC4/SS1); also elsewhere on the board
BR2: U1.9 (PB2); also elsewhere on the board
BR3: U2.19 (PA3/ADC3/SCK1); also elsewhere on the board
EA1: U1.3 (PA5/ADC5); also elsewhere on the board
EA2: U1.6 (PB5/ADC8/CLKOUT); also elsewhere on the board
EA3: U2.12 (PC0/ADC12/SCK2); also elsewhere on the board
EA4: U2.17 (PA1/ADC1/DO1); also elsewhere on the board
EB1: U1.4 (PA6/ADC6); also elsewhere on the board
EB2: U1.7 (PB4/ADC9/RST); also elsewhere on the board
EB3: U2.13 (PC1/ADC13/DO2); also elsewhere on the board
EB4: U2.18 (PA2/ADC2/DI1); also elsewhere on the board
ES1: U1.5 (PA7/ADC7); also elsewhere on the board
ES2: U1.8 (PB3); also elsewhere on the board
ES3: U1.18 (PA2/ADC2/DI1); also elsewhere on the board
ES4: U1.14 (PC2/ADC14/DI2); also elsewhere on the board
GND: C1.2, C2.2, C3.2, C4.2, J1.3, J3.1, J4.1, J5.1, J6.1, J7.1, J8.1, J9.4, J10.4, U1.20 (GND), U2.20 (GND); also elsewhere on the board
unnamed: J1.1, J2.3, J2.5
SCL: J9.2, J10.2, R112.2, U1.11 (PB0/ADC11/SCL), U2.11 (PB0/ADC11/SCL)
SDA: J9.3, J10.3, R113.2, U1.10 (PB1/ADC10/SDA), U2.10 (PB1/ADC10/SDA)
UPDI1: J2.6, U1.16 (PA0/UPDI/RESET)
UPDI2: J2.4, U2.16 (PA0/UPDI/RESET)
VCC: J2.2, J9.1, J10.1, R112.1, R113.1; also elsewhere on the board
VCC_UPDI: C1.1, C2.1, C3.1, C4.1, J1.2, J2.1, U1.1 (VCC), U2.1 (VCC)

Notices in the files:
hardware/pcbs/rpiconnector/rpiconnector.kicad_sch:
Licensed under CERN-OHL-S v2 or later
